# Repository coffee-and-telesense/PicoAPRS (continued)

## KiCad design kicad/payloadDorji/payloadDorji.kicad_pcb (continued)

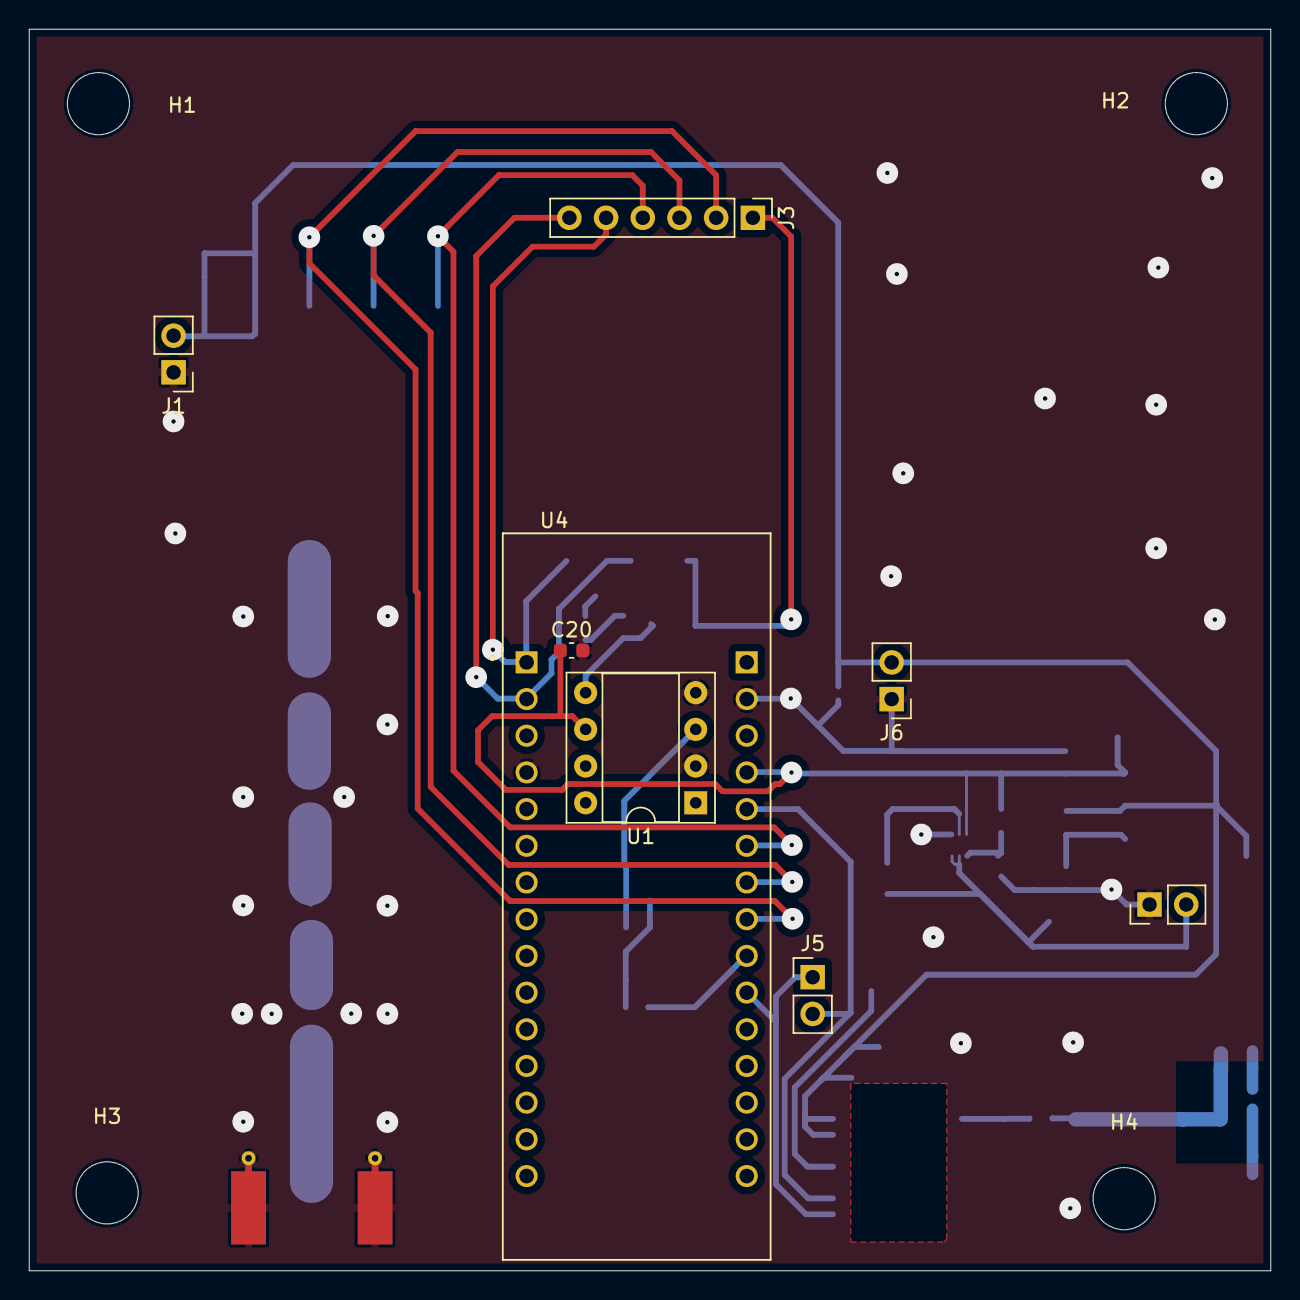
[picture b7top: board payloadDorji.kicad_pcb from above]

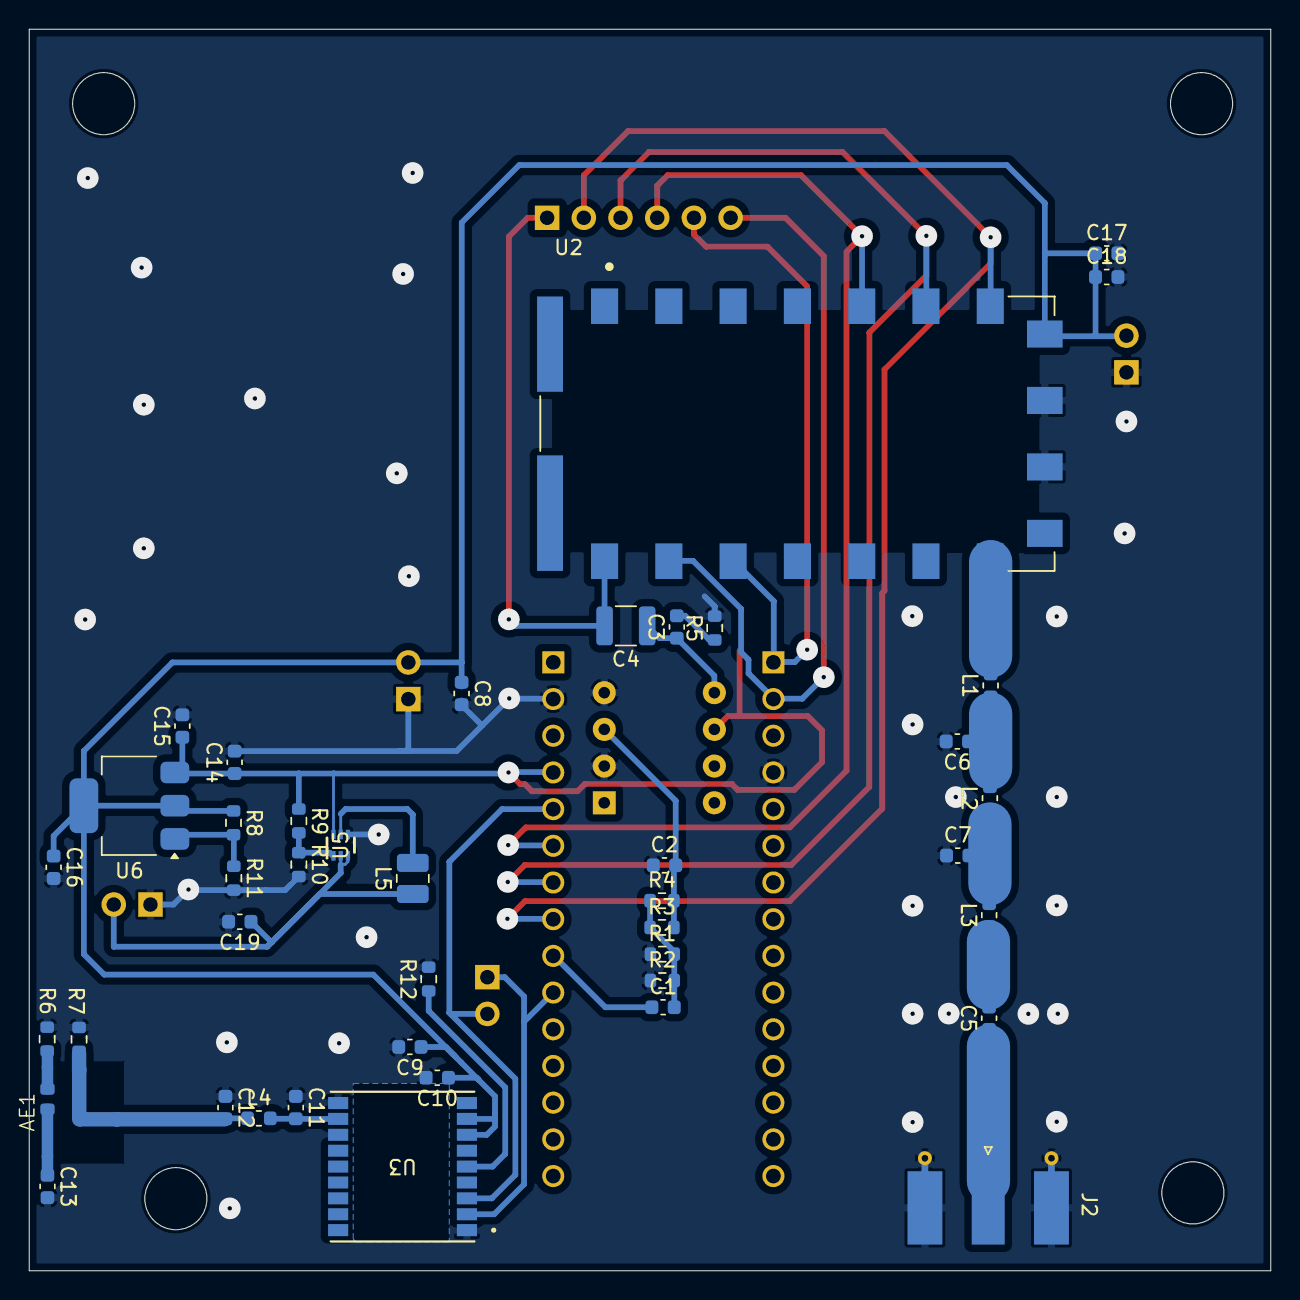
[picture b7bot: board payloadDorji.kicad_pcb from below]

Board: 2 copper layers, 85.9 x 85.9 mm, 54 parts (42 on the bottom side), 29 nets.

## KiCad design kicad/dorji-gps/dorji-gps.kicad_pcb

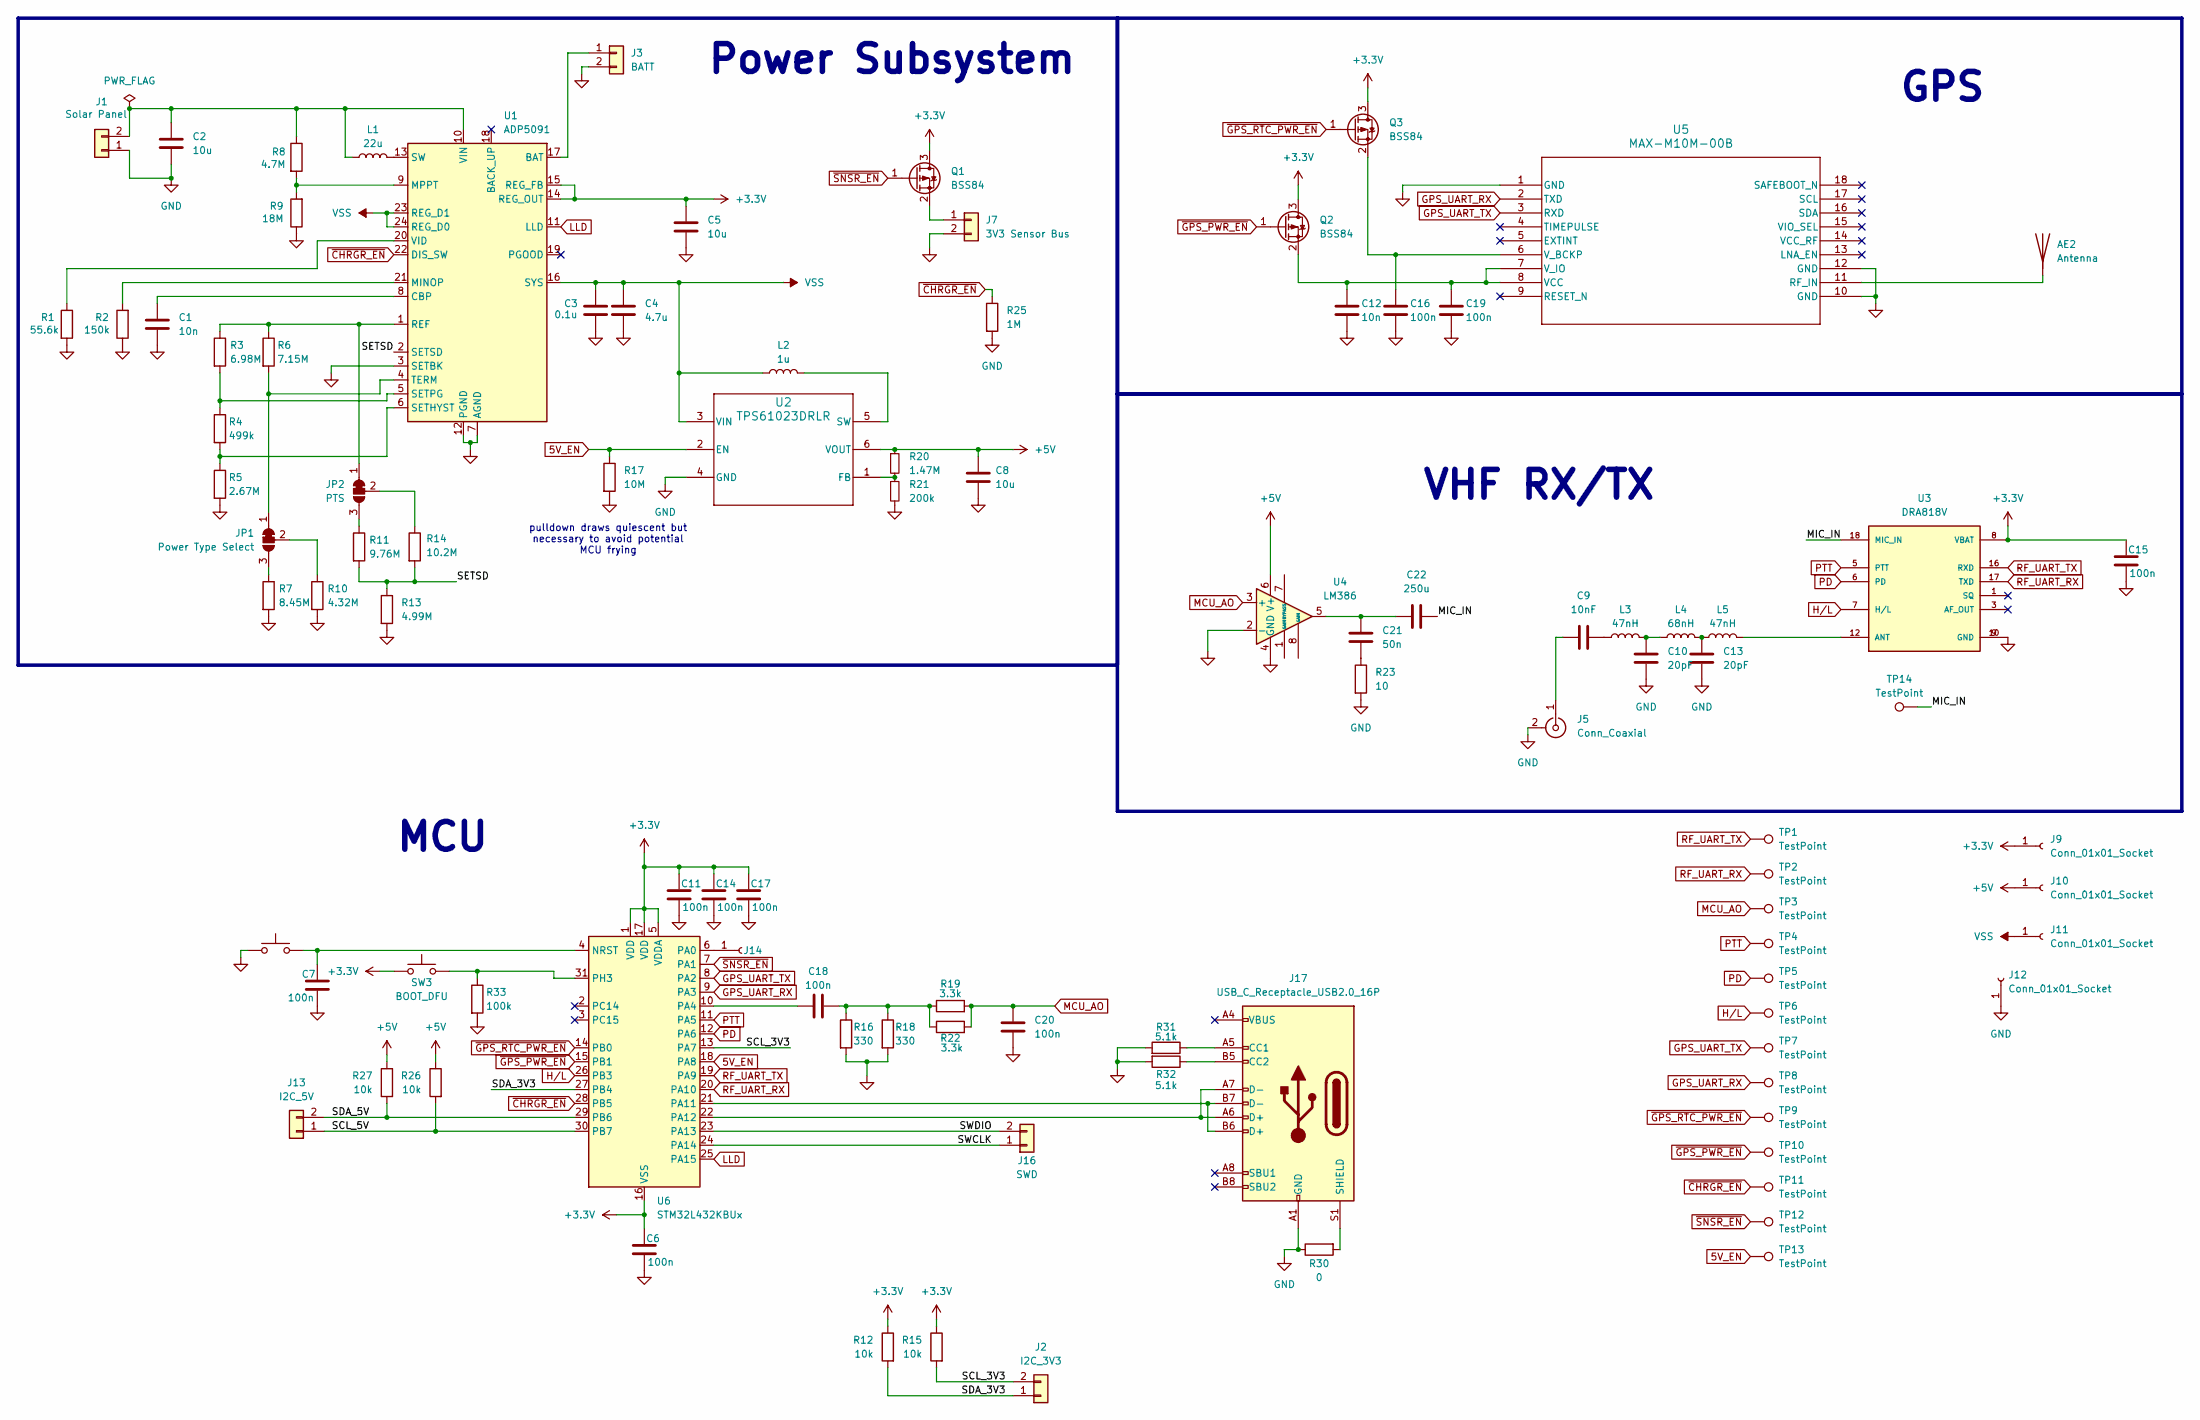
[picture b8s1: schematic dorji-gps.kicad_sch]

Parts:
AE2: Antenna
C1, C12: 10n
C2, C5, C8: 10u
C3: 0.1u
C4: 4.7u
C6, C7, C11, C14, C15, C16, C17, C19: 100n
C9: 10nF; C_0603_1608Metric
C10, C13: 20pF; C_0603_1608Metric
C18, C20: 100n; C_0603_1608Metric
C21: 50n; C_0603_1608Metric
C22: 250u; C_1210_3225Metric
J1: Solar Panel
J2: I2C_3V3
J3: BATT
J5: Conn_Coaxial; SMA_Molex_73251-1153_EdgeMount_Horizontal
J7: 3V3 Sensor Bus
J9, J10, J11, J12, J14: Conn_01x01_Socket
J13: I2C_5V
J16: SWD
J17: USB_C_Receptacle_USB2.0_16P
JP1: Power Type Select
JP2: PTS
L1: 22u
L2: 1u
L3, L5: 47nH; L_0603_1608Metric
L4: 68nH; L_0603_1608Metric
Q1, Q2, Q3: BSS84; SOT-23
R1: 55.6k
R2: 150k
R3: 6.98M
R4: 499k
R5: 2.67M
R6: 7.15M
R7: 8.45M
R8: 4.7M
R9: 18M
R10: 4.32M
R11: 9.76M
R12, R15, R26, R27: 10k
R13: 4.99M
R14: 10.2M
R16, R18: 330
R17: 10M
R19, R22: 3.3k; R_0603_1608Metric
R20: 1.47M
R21: 200k
R23: 10; R_0603_1608Metric
R25: 1M
R30: 0
R31, R32: 5.1k
R33: 100k
SW3: BOOT_DFU
SW4: RST
TP1, TP2, TP3, TP4, TP5, TP6, TP7, TP8, TP9, TP10, TP11, TP12, TP13, TP14: TestPoint
U1: ADP5091; LFCSP-24-1EP_4x4mm_P0.5mm_EP2.3x2.3mm
U2: TPS61023DRLR; DRL0006A
U3: DRA818V; DORJI_DRA818V; PART_REV 1.23
U4: LM386; DIP-8_W7.62mm_Socket
U5: MAX-M10M-00B; MOD18_MAX-M10M_UBL
U6: STM32L432KBUx; QFN-32-1EP_5x5mm_P0.5mm_EP3.45x3.45mm

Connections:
5V_EN: R17.1, TP13.1, U2.2 (EN), U6.18 (PA8)
+5V: C8.1, J10.1, R20.1, R26.1, R27.1, U2.6 (VOUT), U4.6 (V+)
/MIC_IN: C22.2, TP14.1, U3.18 (MIC_IN)
/SCL_3V3: J2.2, R15.2, U6.13 (PA7)
/SCL_5V: J13.1, R26.2, U6.30 (PB7)
/SDA_3V3: J2.1, R12.2, U6.27 (PB4)
/SDA_5V: J13.2, R27.2, U6.29 (PB6)
/SETSD: R11.2, R13.1, R14.2, U1.2 (SETSD)
/SWCLK: J16.1, U6.24 (PA14)
/SWDIO: J16.2, U6.23 (PA13)
GPS_UART_RX: TP8.1, U5.2 (TXD), U6.9 (PA3)
GPS_UART_TX: TP7.1, U5.3 (RXD), U6.8 (PA2)
H/L: TP6.1, U3.7 (H/L), U6.26 (PB3)
LLD: U1.11 (LLD), U6.25 (PA15)
MCU_AO: C20.2, R19.2, R22.2, TP3.1, U4.3 (+)
unnamed: C9.2, L3.1
unnamed: C10.2, L3.2, L4.1
unnamed: C13.1, L4.2, L5.1
unnamed: C18.2, R16.1, R18.1, R19.1, R22.1
unnamed: C21.1, C22.1, U4.5
unnamed: C21.2, R23.1
unnamed: C2.1, J1.2, L1.1, R8.1, U1.10 (VIN)
unnamed: J3.1, U1.17 (BAT)
unnamed 25: J17.A6 (D+), J17.A7 (D-), U6.22 (PA12); also elsewhere on the board
unnamed 26: J17.B6 (D+), J17.B7 (D-), U6.21 (PA11); also elsewhere on the board
unnamed 27: J17.S1 (SHIELD), R30.2; also elsewhere on the board
unnamed: C9.1, J5.1 (In)
unnamed: J7.1, Q1.2 (S)
unnamed: J14.1, U6.6 (PA0)
unnamed: J17.A4 (VBUS), J17.A9 (VBUS), J17.B4 (VBUS), J17.B9 (VBUS)
unnamed: J17.A5 (CC1), R31.1
unnamed: J17.B5 (CC2), R32.1
unnamed: JP1.1 (A), R6.2, U1.4 (TERM)
unnamed: JP1.3 (B), R7.1
unnamed: JP1.2 (C), R10.1
unnamed: JP2.1 (A), R3.1, R6.1, U1.1 (REF)
unnamed: JP2.3 (B), R11.1
unnamed: JP2.2 (C), R14.1
unnamed: C12.1, C19.1, Q2.2 (S), U5.7 (V_IO), U5.8 (VCC)
unnamed: C16.1, Q3.2 (S), U5.6 (V_BCKP)
unnamed: C1.1, U1.8 (CBP)
unnamed: R2.2, U1.21 (MINOP)
unnamed: R8.2, R9.2, U1.9 (MPPT)
unnamed: R4.2, R5.1, U1.6 (SETHYST)
unnamed: R3.2, R4.1, U1.5 (SETPG)
unnamed: L1.2, U1.13 (SW)
unnamed: R1.1, U1.20 (VID)
unnamed: R20.2, R21.1, U2.1 (FB)
unnamed: L2.2, U2.5 (SW)
unnamed: L5.2, U3.12 (ANT)
unnamed 52: AE2.1, U5.11 (RF_IN); also elsewhere on the board
unnamed: C7.1, SW4.1, U6.4 (NRST)
unnamed: C18.1, U6.10 (PA4)
unnamed: R33.1, SW3.1, U6.31 (PH3)
PD: TP5.1, U3.6 (PD), U6.12 (PA6)
PTT: TP4.1, U3.5 (PTT), U6.11 (PA5)
RF_UART_RX: TP2.1, U3.17 (TXD), U6.20 (PA10)
RF_UART_TX: TP1.1, U3.16 (RXD), U6.19 (PA9)
VSS: C3.1, C4.1, J11.1, L2.1, U1.16 (SYS), U1.23 (REG_D1), U1.24 (REG_D0), U2.3 (VIN)
~CHRGR_EN: R25.1, TP11.1, U1.22 (DIS_SW), U6.28 (PB5)
~GPS_PWR_EN: Q2.1 (G), TP10.1, U6.15 (PB1)
~GPS_RTC_PWR_EN: Q3.1 (G), TP9.1, U6.14 (PB0)
~SNSR_EN: Q1.1 (G), TP12.1, U6.7 (PA1)

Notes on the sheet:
GPS
VHF RX/TX
Power Subsystem
MCU
pulldown draws quiescent but necessary to avoid potential MCU frying

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
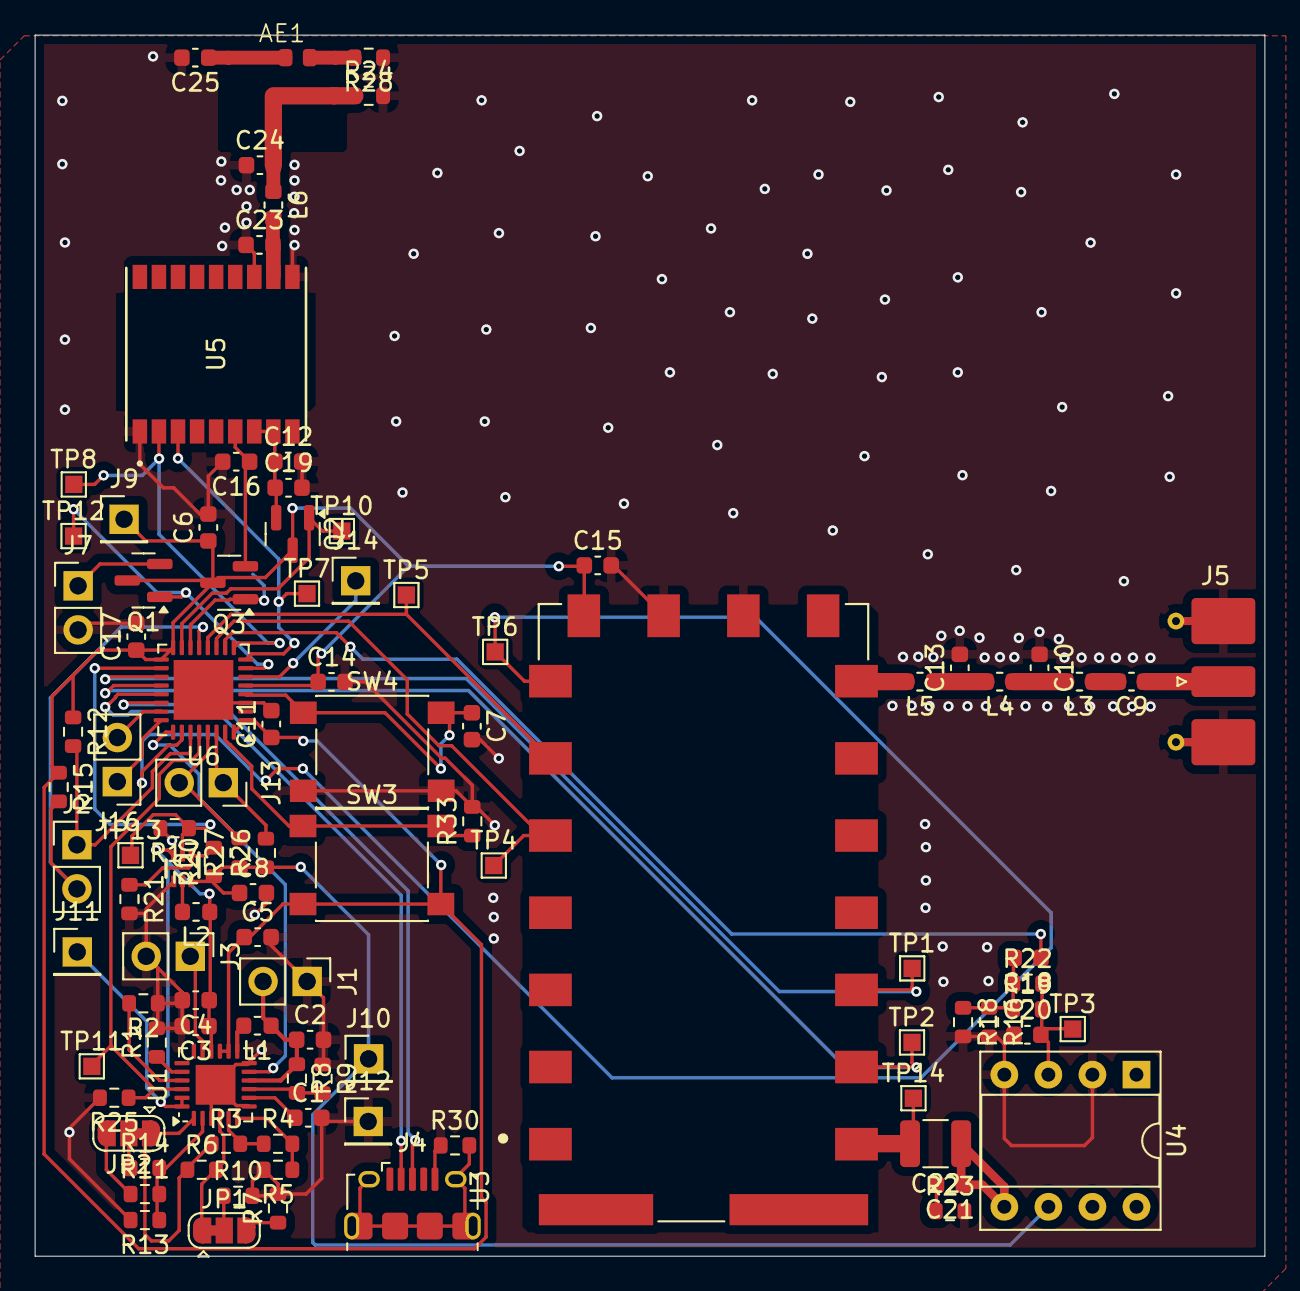
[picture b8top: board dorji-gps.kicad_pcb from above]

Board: 2 copper layers, 70.9 x 70.4 mm, 102 parts (1 on the bottom side), 64 nets.

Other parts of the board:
AE1: Antenna; AC30157-01 GNSS Ceramic Chip
C23, C24: DNP; C_0603_1608Metric
C25: 10p; C_0603_1608Metric
J4: USB_B_Micro; USB_Micro-B_Amphenol_10118194-0001LF_Horizontal
L6: 2.0n; L_0603_1608Metric
R24, R28: 0; R_0603_1608Metric

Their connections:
unnamed: AE1.1 (A), C25.1, R28.2
unnamed: C24.2, L6.1, R24.1
unnamed 25: J4.3 (D+); also elsewhere on the board
unnamed 26: J4.2 (D-); also elsewhere on the board
unnamed 27: J4.6 (Shield); also elsewhere on the board
unnamed 52: C23.2, L6.2; also elsewhere on the board

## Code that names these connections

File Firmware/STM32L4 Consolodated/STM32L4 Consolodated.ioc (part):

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Mcu.Name=STM32L432K(B-C)Ux
Mcu.Package=UFQFPN32
Mcu.UserName=STM32L432KCUx
PA0.GPIOParameters=GPIO_Label
PA0.GPIO_Label=MCO [High speed clock in]
PA0.Mode=HSE-External-Clock-Source-for-LittleOrca
PA0.Signal=RCC_CK_IN
PA10.Mode=Asynchronous
PA10.Signal=USART1_RX
PA13\ (JTMS-SWDIO).GPIOParameters=GPIO_Label
PA13\ (JTMS-SWDIO).GPIO_Label=SWDIO
PA13\ (JTMS-SWDIO).Mode=Serial_Wire
PA13\ (JTMS-SWDIO).Signal=SYS_JTMS-SWDIO
PA14\ (JTCK-SWCLK).GPIOParameters=GPIO_Label
PA14\ (JTCK-SWCLK).GPIO_Label=SWCLK
PA14\ (JTCK-SWCLK).Mode=Serial_Wire
PA14\ (JTCK-SWCLK).Signal=SYS_JTCK-SWCLK
PA15\ (JTDI).GPIOParameters=GPIO_Label
PA15\ (JTDI).GPIO_Label=VCP_RX
PA15\ (JTDI).Mode=Asynchronous
PA15\ (JTDI).Signal=USART2_RX
PA2.GPIOParameters=GPIO_Label
PA2.GPIO_Label=VCP_TX
PA2.Mode=Asynchronous
PA2.Signal=USART2_TX
PA4.Signal=COMP_DAC11_group
PA5.Signal=GPIO_Output
PA6.Signal=GPIO_Output
PA7.Signal=GPIO_Output
PA9.Mode=Asynchronous
PA9.Signal=USART1_TX
PB3\ (JTDO-TRACESWO).GPIOParameters=GPIO_Label
PB3\ (JTDO-TRACESWO).GPIO_Label=LD3 [Green]
PB3\ (JTDO-TRACESWO).Signal=GPIO_Output
PC14-OSC32_IN\ (PC14).Mode=LSE-External-Oscillator
PC14-OSC32_IN\ (PC14).Signal=RCC_OSC32_IN
PC15-OSC32_OUT\ (PC15).Mode=LSE-External-Oscillator
PC15-OSC32_OUT\ (PC15).Signal=RCC_OSC32_OUT
RCC.HSE_VALUE=8000000
RCC.SYSCLKFreq_VALUE=32000000
RCC.SYSCLKSource=RCC_SYSCLKSOURCE_PLLCLK
board=NUCLEO-L432KC
boardIOC=true

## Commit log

2024-09-12 init
2024-09-12 symbols
2024-09-12 clean gerbers
2024-09-12 clean sch
2024-09-12 clean sch2
2024-09-14 gnss board
2024-09-14 powerTest files
2024-09-14 fix structure
2024-09-14 remove extra files
2024-10-03 dorji payload files
2024-10-04 dorji edition board
2024-10-04 DRA818V symbol and footprint
2024-10-07 the layout doesn't work in the alser
2024-10-09 L4 nucleo symbols
2024-10-09 payloadDorji add gps and power
2024-10-14 some fixes, not done yet
2024-10-15 no blow up
2024-10-18 ube 2
2024-10-18 test
2024-10-21 mounting holes, vias, etc
2024-10-21 kiCAD cleanup! Added .gitignore file, removed temporary files from git, fixed library paths to be relative, cleaned up schematic errors, cleaned up layout errors, cleaned up consistency between sch/b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
2024-10-21 restructured git repo. .Sym files are located in the symbols dir. footprints in the picoaprs.pretty dir within the symbols dir
2024-10-21 deleted redundant dirs, continued restructure
2024-10-22 add lib dir
2024-10-22 deleted immature dir
2024-10-22 Fixed library paths. Add PICOAPRS_LIBRARIES to your project variables which points to the kicad/lib directory. Also fixed up schematic to be more readable, and fixed some more issues between sch/brd.
2024-10-22 ublox symbol
2024-10-22 Fixed GPS symbol (blech) and found two misconnected pins. Fixed in shcematic and layout.
2024-10-22 Fix final missing footprints! OK, NOW everything is fixed.
2024-12-05 working arduino example for GPS. Runs on dorjiPayload layout
2024-12-05 forgot the .ino
2025-01-17 Delete Firmware/stmBlink/Core/Inc/device.h
    its fucked
2025-01-24 Power Board Test 1.1
    Updated Test Power Board
2025-02-12 power test resistor change
2025-02-12 Si4463 Transceiver Circuit V2.
    Updated the transceiver board to make it compliant with EPL fab limitations. Fixed all GND vias, added Header Pins for the GPIO pins
2025-02-16 move some vias on rf frontend test board
2025-02-16 reroute rf_en on rf frontend test for assembly ease
2025-02-17 slight value changes to rf frontend
2025-02-19 GNSS board V2
    This new board is a review of the pre existing GNSS circuitry used with the Dorji circuit. Fixed all DRC errors and implemented via snitching compatible with EPL Fab constraints.
2025-02-19 GNSS V2.1
    Fixed footprint of antenna
2025-03-05 kicad 9.0 updates
2025-04-11 BOM of second Transceiver board
    BOM of second Transceiver board
2025-04-18 bring updated boards into final design
2025-04-18 update GPS to I2C
2025-04-20 PCB layout of System Board v1.01
2025-04-23 Finished PCB layoiut of Integration board V1.01
2025-04-23 slight changes to mainboard, rf0603 layout
2025-04-28 improved layout, added PGOOD to MCU connection
2025-05-17 Integration Board V3
    Replaced USB C receptacle with Pinout for breakout board, Solved all thermal issues, VSS = GND for STM microcontroller, updated transceiver module to 0603 pads for RLC components
2025-05-17 USB C Breakout boards inhouse
    Breakout boards for usb C 2.0
2025-05-19 main board updates, stm breakout
2025-05-22 Integration Boards V3.5
    Fixed places prone to shorts and started adding header labels and fixing component labels on the silkscreen layer
2025-05-30 Silscreen layer fixed
    Last Integrtion board V5
2025-05-30 via stitch updates
2025-05-30 Fixed small issues
2025-06-03 rev b final JLC
2025-06-20 transistors backwards
2025-07-01 rev1 not complete
2025-07-03 rev C(ompact) pre-review
2025-07-08 rev C pre-review 2
